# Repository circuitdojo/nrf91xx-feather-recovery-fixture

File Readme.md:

# Overview

Simplify your development process with this compact, 3D-printed programming fixture designed specifically for the nRF9160 and nRF9151 Feather boards.

This fixture enables seamless programming by simply placing your board on top for quick connections. Compatible with both 10-pin JTAG programmers and Raspberry Pi Picoprobe, this tool fits perfectly into your workflow. (Programmer sold separately)

Whether you’re a hobbyist or professional developer, this open-source design ensures flexibility and accessibility. Bring ease to your prototyping and programming with a reliable, user-friendly fixture.

## Where to Buy

You can purchase the Recovery Fixture from the [Circuit Dojo Store](https://www.circuitdojo.com/products/recovery-fixture).

## License

[CERN Open Hardware Licence Version 2 - Weakly Reciprocal](https://github.com/circuitdojo/nrf91xx-feather-recovery-fixture#CERN-OHL-W-2.0-1-ov-file)

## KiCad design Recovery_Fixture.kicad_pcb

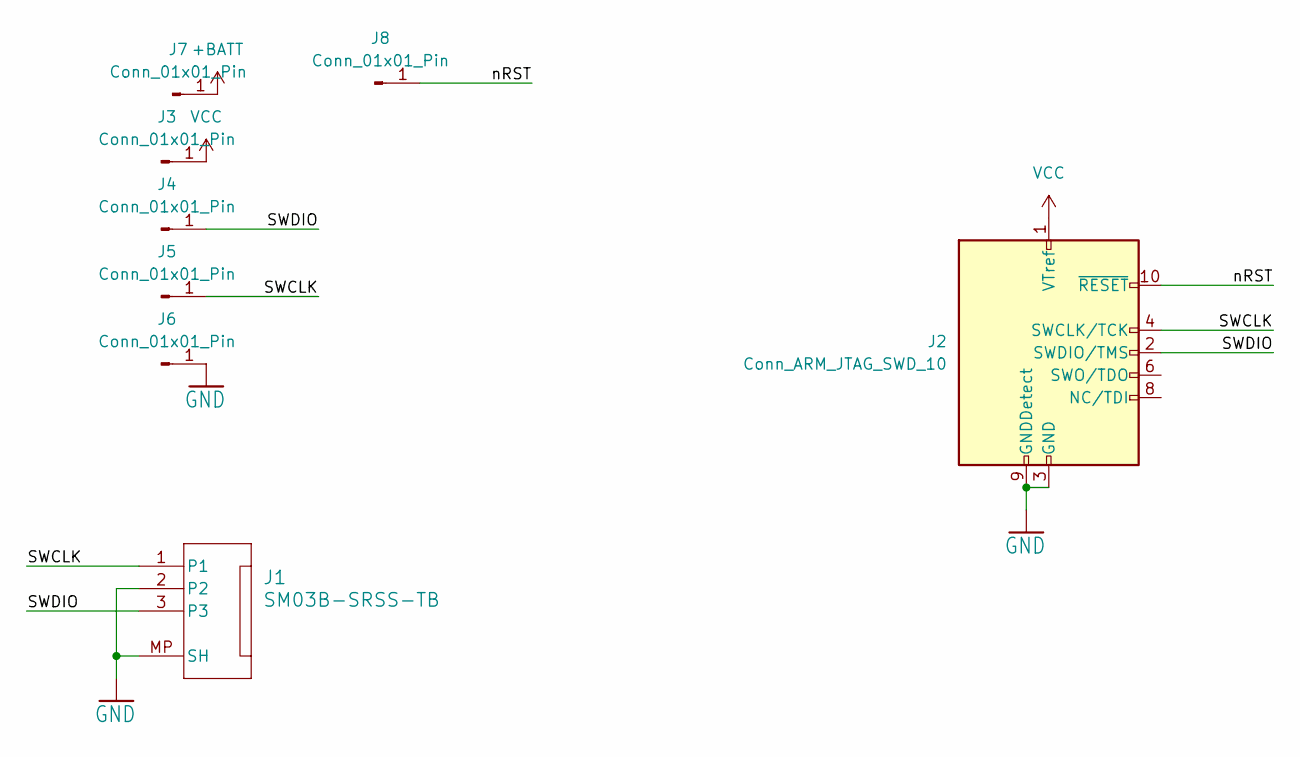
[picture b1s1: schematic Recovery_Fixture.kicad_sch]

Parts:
J1: SM03B-SRSS-TB; JST_SH_SM03B-SRSS-TB_1x03-1MP_P1.00mm_Horizontal
J2: Conn_ARM_JTAG_SWD_10; PinHeader_2x05_P1.27mm_Vertical_SMD
J3, J4, J5, J6, J7, J8: Conn_01x01_Pin; TestPoint_THTPad_D2.5mm_Drill1.2mm

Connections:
+BATT: J7.1
/SWCLK: J1.1, J2.4 (SWCLK/TCK), J5.1
/SWDIO: J1.3, J2.2 (SWDIO/TMS), J4.1
/nRST: J2.10 (~RESET), J8.1
GND: J1.2, J1.MP (SH), J2.3 (GND), J2.5 (GND), J2.9 (GNDDetect), J6.1
VCC: J2.1 (VTref), J3.1

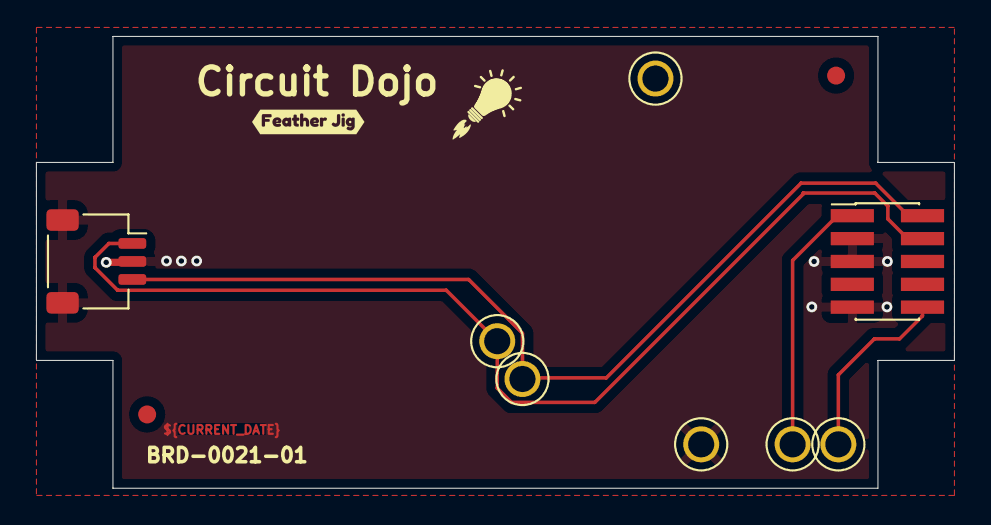
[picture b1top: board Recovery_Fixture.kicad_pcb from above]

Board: 2 copper layers, 51.0 x 25.1 mm, 11 parts (0 on the bottom side), 5 nets.

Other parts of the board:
FID1, FID2: Fiducial_1mm_Mask2mm
kibuzzard-66C4ED28: G***; kibuzzard-66C4ED28

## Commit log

2024-11-07 Initial release
